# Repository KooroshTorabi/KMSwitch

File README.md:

# kmswitch

**One keyboard and mouse for two computers.** A small open-hardware box that sits between your USB
keyboard/mouse (or a wireless dongle, or a hub) and two PCs. Switch with a hotkey, or just push the
mouse off the edge of one screen and it appears on the other. No software on either PC, works in the
BIOS, and the two PCs stay galvanically isolated.

| | |
|---|---|
| Switching | hotkey (default **Win+F12**) or moving the pointer across the screen edge |
| Host software | none: the PCs see a normal USB keyboard + mouse (+ a small USB drive) |
| BIOS / boot | yes: HID Boot Protocol keyboard and mouse |
| Input | one USB-A port for any keyboard, mouse or dongle; use a hub for several devices |
| Shared drive | microSD card, shown as a USB drive on whichever PC is active |
| Power | 5 V USB-C adapter (2-3 A), so the keyboard works even if PC 1 is off |
| Isolation | CA-IS3721 digital isolator: PC 1 and PC 2 grounds never touch |
| ESD protection | USBLC6-2SC6 on the USB-A port (both variants) and on both PC USB-C ports (variant B) |
| RGB LED (optional) | 3-pin header J6 (5V, DIN, GND) for a WS2812/SK6812 LED or strip, for your own case design |

> **Status:** hardware rev 1.0 and firmware 1.0 are complete but not yet built or tested on real boards. See *Before you order* below and [firmware/README.md](firmware/README.md).

## What it does

<table>
<tr>
<td width="50%"><br>
<b>1. Copy files between the PCs</b><br>
The box's microSD card shows up as a USB drive on the active PC. Save a file there, switch, and open it on the other PC. No network or cloud needed.</td>
<td width="50%"><br>
<b>2. Switch by moving the mouse</b><br>
Push the pointer past the edge of PC 1's screen and it appears on PC 2, and the keyboard follows. You arrange the screens once on the settings page, like the monitor layout in Windows.</td>
</tr>
<tr>
<td><br>
<b>3. Switch from the keyboard</b><br>
<b>Win + F12</b> (or any key you choose) switches keyboard and mouse together. The PCs never see the hotkey. It works in the BIOS and at the login screen.</td>
<td><br>
<b>4. Game mode</b><br>
<b>Win + F11</b> switches the active PC to relative mouse movement, which games, Blender and remote-desktop tools need. Edge switching pauses so a fast flick never jumps to the other PC.</td>
</tr>
<tr>
<td><br>
<b>5. RGB LED connection</b><br>
Header J6 drives a WS2812 / SK6812 LED or short strip, lit in the colour of the active PC. Good for your own case or a desk light.</td>
<td><br>
<b>6. Separate power, isolated PCs</b><br>
The box runs from its own 5 V USB-C adapter, so the keyboard keeps working when PC 1 is off. A digital isolator keeps the grounds of the two PCs apart (no ground loops).</td>
</tr>
</table>

> Clipboard copy-paste of text would need a program on each PC. kmswitch deliberately needs no software on the PCs, so it shares files through the drive instead.

## How it works

```
 keyboard / mouse / dongle / hub
              |
          [USB-A]
              |
   MCU-A (RP2040, USB host via PIO-USB) ---- USB device ----> PC 1
              |
       UART through CA-IS3721 isolator
              |
   MCU-B (RP2040) -------------------------- USB device ----> PC 2
```

- MCU-A reads your input devices as a USB host. It sends each report either to PC 1 directly or over the isolated UART to MCU-B, which sends it to PC 2.
- To each PC, its MCU looks like a plain USB keyboard + mouse (Boot Protocol), so it works in BIOS/UEFI, login screens and any OS, with no drivers.
- **Screen-edge switching:** the mouse is reported with absolute coordinates, so the box knows when the pointer reaches the edge and hands it over to the other PC.
- **Shared drive:** the microSD card appears as a USB drive on the active PC only. On a switch the drive is ejected and shown to the other PC (media change), so the file system is never mounted twice.

## Two board variants, one choice

Both variants have the same features, the same GPIO map (so one firmware fits both) and connectors in the same places.

| | **Variant A** - RP2040-Zero carrier | **Variant B** - 2x RP2040 chip-down |
|---|---|---|
| Folder | `hardware/variant-a-rp2040-zero` | `hardware/variant-b-rp2040` |
| Board | 80 x 48 mm, 2 layers | 80 x 54 mm, 2 layers |
| MCUs | two Waveshare RP2040-Zero modules on pin headers | two RP2040 + W25Q16 flash + 12 MHz crystal |
| Assembly | hand-solderable (0805, SOIC, SOD-123, SOT-23-6) | factory assembly (JLCPCB BOM + CPL included) |
| PC connections | USB-C on the modules | USB-C on the board |
| Powered without adapter | no | yes, from PC 1 (adapter and PC 1 are OR-ed by diodes) |
| Back-feed into a switched-off PC 1 | ~4.7 V can reach PC 1 VBUS through the module | none |
| Good for | building one at home | ordering a batch, smallest result |

## Configuration (optional)

It works without any setup. To tune the mouse for different screens, change the hotkeys or add a relative mode for games, press **Win+F10**: the box opens its own settings page (`http://192.168.7.1`, served by the box over a private USB network link, any browser, nothing installed). You place PC 2 next to PC 1 by dragging, like monitors in the OS display settings, and the pointer crosses only where the screens touch. Changes are saved on the box by themselves, the page shows live which PC is connected, and the box measures each PC's monitors automatically (LEDs blink for a few seconds while it switches over and measures), including several monitors of different shape on one PC.
Where the USB network is not allowed, the same page works offline from the microSD card ([`config/KMSWITCH.HTM`](config/KMSWITCH.HTM)) together with the settings file [`config/KMSWITCH.TXT`](config/KMSWITCH.TXT).
Full reference: [docs/configuration.md](docs/configuration.md); page-to-box protocol: [docs/web-api.md](docs/web-api.md).

**Firmware updates** come from the same page (one click when a new release is out, confirmed with **Win+F8** on the box's own keyboard), from a file copied to the drive, or, as a last resort, through the RP2040's BOOTSEL mode. Updates are signed and roll back by themselves if the new version does not start: [docs/firmware-update.md](docs/firmware-update.md).

## Schematics

Each variant has one readable sheet, split into framed blocks (power input, USB ports, MCU, microSD, isolation, ...) with real wires inside each block, named power symbols (`+5V_IN`, `+3V3_A`, `GND_B`, ...) and net labels between blocks.
PDF: `hardware/<variant>/fab/kmswitch-<a|b>-schematic.pdf`. Vector versions that stay sharp at any zoom: [variant A (SVG)](docs/schematic-a.svg), [variant B (SVG)](docs/schematic-b.svg).

**Variant A** (A3 sheet), click for full size:

**Variant B** (A2 sheet), click for full size:

## Repository layout

```
hardware/
  lib/                         project symbols (RP2040-Zero, microSD), RP2040-Zero footprint,
                               3dmodels/ (detailed STEP models for parts that have none in the KiCad library)
  variant-a-rp2040-zero/       KiCad project + fab/ (gerbers zip, BOM, CPL, schematic PDF, renders)
  variant-b-rp2040/            KiCad project + fab/
config/
  KMSWITCH.TXT                 default settings file for the microSD card
  KMSWITCH.HTM                 settings page (served by the box, or offline from the card)
enclosure/
  kmswitch_case.scad           parametric 3D-printable case (variant = "A" or "B")
  stl/                         ready-to-print bottom + lid for both variants
firmware/                      (to come) firmware sources, latest.json and released update files
tools/                         Python scripts that generate the schematics, boards and outputs
docs/                          board and case renders, turntable animation, DRC reports
```

The KiCad files are saved by KiCad 7 and open in KiCad 7, 8 and 9 (newer versions convert them on save).

## Pin map (both variants)

| Function | MCU-A (host side, PC 1) | MCU-B (PC 2) |
|---|---|---|
| USB host D+ / D- (PIO-USB) | GP2 / GP3 (22 Ω series) | - |
| UART1 TX / RX (via isolator) | GP4 / GP5 | GP4 / GP5 |
| microSD SCK / MOSI / MISO / CS (SPI1) | GP14 / GP15 / GP28 / GP29 | - |
| microSD card detect | GP26 (switch to GND, use pull-up) | - |
| Status LED | GP16 WS2812 (A) / GP16-18 red, green, blue LEDs (B) | same |
| PC 1 VBUS sense (B only) | GP24 (10k/20k divider) | - |
| External RGB LED data (header J6) | GP6 (330 Ω series) | - |

PIO-USB needs D- on the pin right after D+ and a system clock that is a multiple of 12 MHz (120 MHz works).

## Building

### Variant A (hand soldering)
1. Order the PCB with `fab/kmswitch-a-gerbers.zip` (2 layers, 1.6 mm, any colour).
2. Solder the SMD parts first (`fab/kmswitch-a-bom.csv`), then the USB-A socket.
3. Solder two 1x9 male headers per module into the carrier, put the RP2040-Zero modules on top and solder them.
   Only the two long rows are used; the five pads on the module's short edge stay free.
4. The modules' USB-C ports go to the PCs. The board's own USB-C is power only (5 V adapter).

### Variant B (factory assembly)
1. Upload `fab/kmswitch-b-gerbers.zip`, `fab/kmswitch-b-bom.csv` and `fab/kmswitch-b-cpl-jlcpcb.csv` to JLCPCB (or similar).
   Every assembled part has an LCSC / JLCPCB part number in the BOM (table in `tools/export.py`). Stock changes, so check them in the JLCPCB part search before ordering. Parts marked `n/a` are not on LCSC and are hand-soldered: the RP2040-Zero modules (variant A), the through-hole USB-A (Molex 67643-0910) and the optional RGB header J6.
   In the JLCPCB placement preview, check that pin 1 of U4-U6 (SOT-23-6), U12 / U52 (SOT-23-5) and the LEDs sits on the marked pad; fix the rotation there if not.
2. Solder the USB-A socket yourself if your assembler does not place through-hole parts.
3. First flash: hold **BOOT**, tap **RST**, and drag the `.uf2` onto the drive that appears. SWD pads are next to the buttons.

### Optional RGB LED
Header **J6** (2.54 mm, labelled *RGB*): pin 1 = 5 V, pin 2 = data (GP6 of MCU-A through 330 Ω), pin 3 = GND.
Connect one WS2812B/SK6812 LED or a short chain, for example to light the side of the active PC or to glow through your own case.
Most WS2812B/SK6812 parts accept the 3.3 V data level at 5 V supply; keep the wire short (under ~20 cm). A short strip draws up to 60 mA per LED at full white, so stay within a few LEDs.
The header is not populated by the assembler; solder pins or a cable if you need it.

### Enclosure

Print `enclosure/stl/kmswitch-<a|b>-bottom.stl` and `-lid.stl` (PLA/PETG, 0.2 mm layers, no supports; the lid prints upside down).
Outside size: 85 x 53 x 21.6 mm (A) or 85 x 59 x 19.6 mm (B). Both parts together use about 35 g of filament and print in about 40 min on a fast printer (1 to 1.5 h on a Prusa MK3S / Ender 3).
Use white or translucent filament for the lid if you want the LEDs to shine through the thin windows.
Fix board and lid with four **M2.5 self-tapping screws**: 20 mm for variant A, 18 mm for variant B. They go through the lid posts and the board into the standoffs.
To change anything (wall thickness, port sizes, height), open `kmswitch_case.scad` in OpenSCAD and edit the parameters at the top.

## Before you order (please read)

- **RP2040-Zero footprint:** the header rows are drawn 15.24 mm apart with 2.54 mm pitch, pad 1 (5V) next to the USB-C.
  Measure your module or print `fab/kmswitch-a-front.png` at 1:1 and check before ordering.
- **Isolator speed:** CA-IS3721**HS** (or ADuM1201**B/C**) is fast enough for a 3 Mbaud UART. The plain ADuM1201**AR** is limited to about 1 Mbaud.
- **ERC:** KiCad 7's command line has no ERC, so the schematic was checked by comparing its netlist with the design scripts (0 differences).
  Run *Inspect → Electrical Rules Checker* once in KiCad; only "power pin not driven" style warnings should remain.
- **DRC:** both boards pass DRC with 0 errors and 0 unconnected pads, checked with KiCad 7. Two warning types are switched off on purpose: silkscreen on the board edge (connectors sit on the edge) and *footprint does not match library* (the 3D models were replaced with the ones in `hardware/lib/3dmodels`).
- The routing comes from an autorouter. It is electrically complete; tidying it by hand is welcome.

## Regenerating

```
cd tools
python3 make_lib.py           # project library
python3 sch_build.py a        # schematic only (layout in sch_a.py), checked against the design netlist
python3 build.py a            # schematic + board + autoroute (Freerouting) + DRC for variant A
python3 build.py b
python3 make_models3d.py     # build the detailed 3D models (CadQuery, STEP)
python3 make_models.py       # attach them to both boards
python3 export.py a           # gerbers, BOM, CPL, PDF, renders
openscad -D 'variant="A"' -D 'part="bottom"' -o ../enclosure/stl/kmswitch-a-bottom.stl ../enclosure/kmswitch_case.scad
```
Needs KiCad 7 with its Python module, Java, OpenSCAD and Freerouting 1.9 (put `freerouting.jar` in `tools/` or set `FREEROUTING_JAR`).
Routing runs Freerouting headless (`xvfb-run`); the result can differ slightly between runs.

## Get a ready-made one

kmswitch is a personal project. I plan to order a small batch of boards; when I have built more units than I need, I can send ready-made ones to people who cannot build one themselves, to wherever I am able to ship.
Please note: **nothing has been ordered or tested yet**, so there are no units today. The more people are interested, the cheaper each unit gets, because boards and assembly cost much less per piece in larger batches.
If you would like one, open an [issue](https://github.com/KooroshTorabi/KMSwitch/issues) titled *"I'd like one"* and say roughly where you are.

## Support the project

This is a personal project that I build in my free time. If you like it and want to help me continue, you can support me here:

- Buy Me a Coffee: https://buymeacoffee.com/kourosh
- Ko-fi: https://ko-fi.com/kourosht

## License

Hardware and enclosure: [CERN-OHL-P-2.0](https://ohwr.org/cern_ohl_p_v2.txt) (permissive). Scripts: MIT.

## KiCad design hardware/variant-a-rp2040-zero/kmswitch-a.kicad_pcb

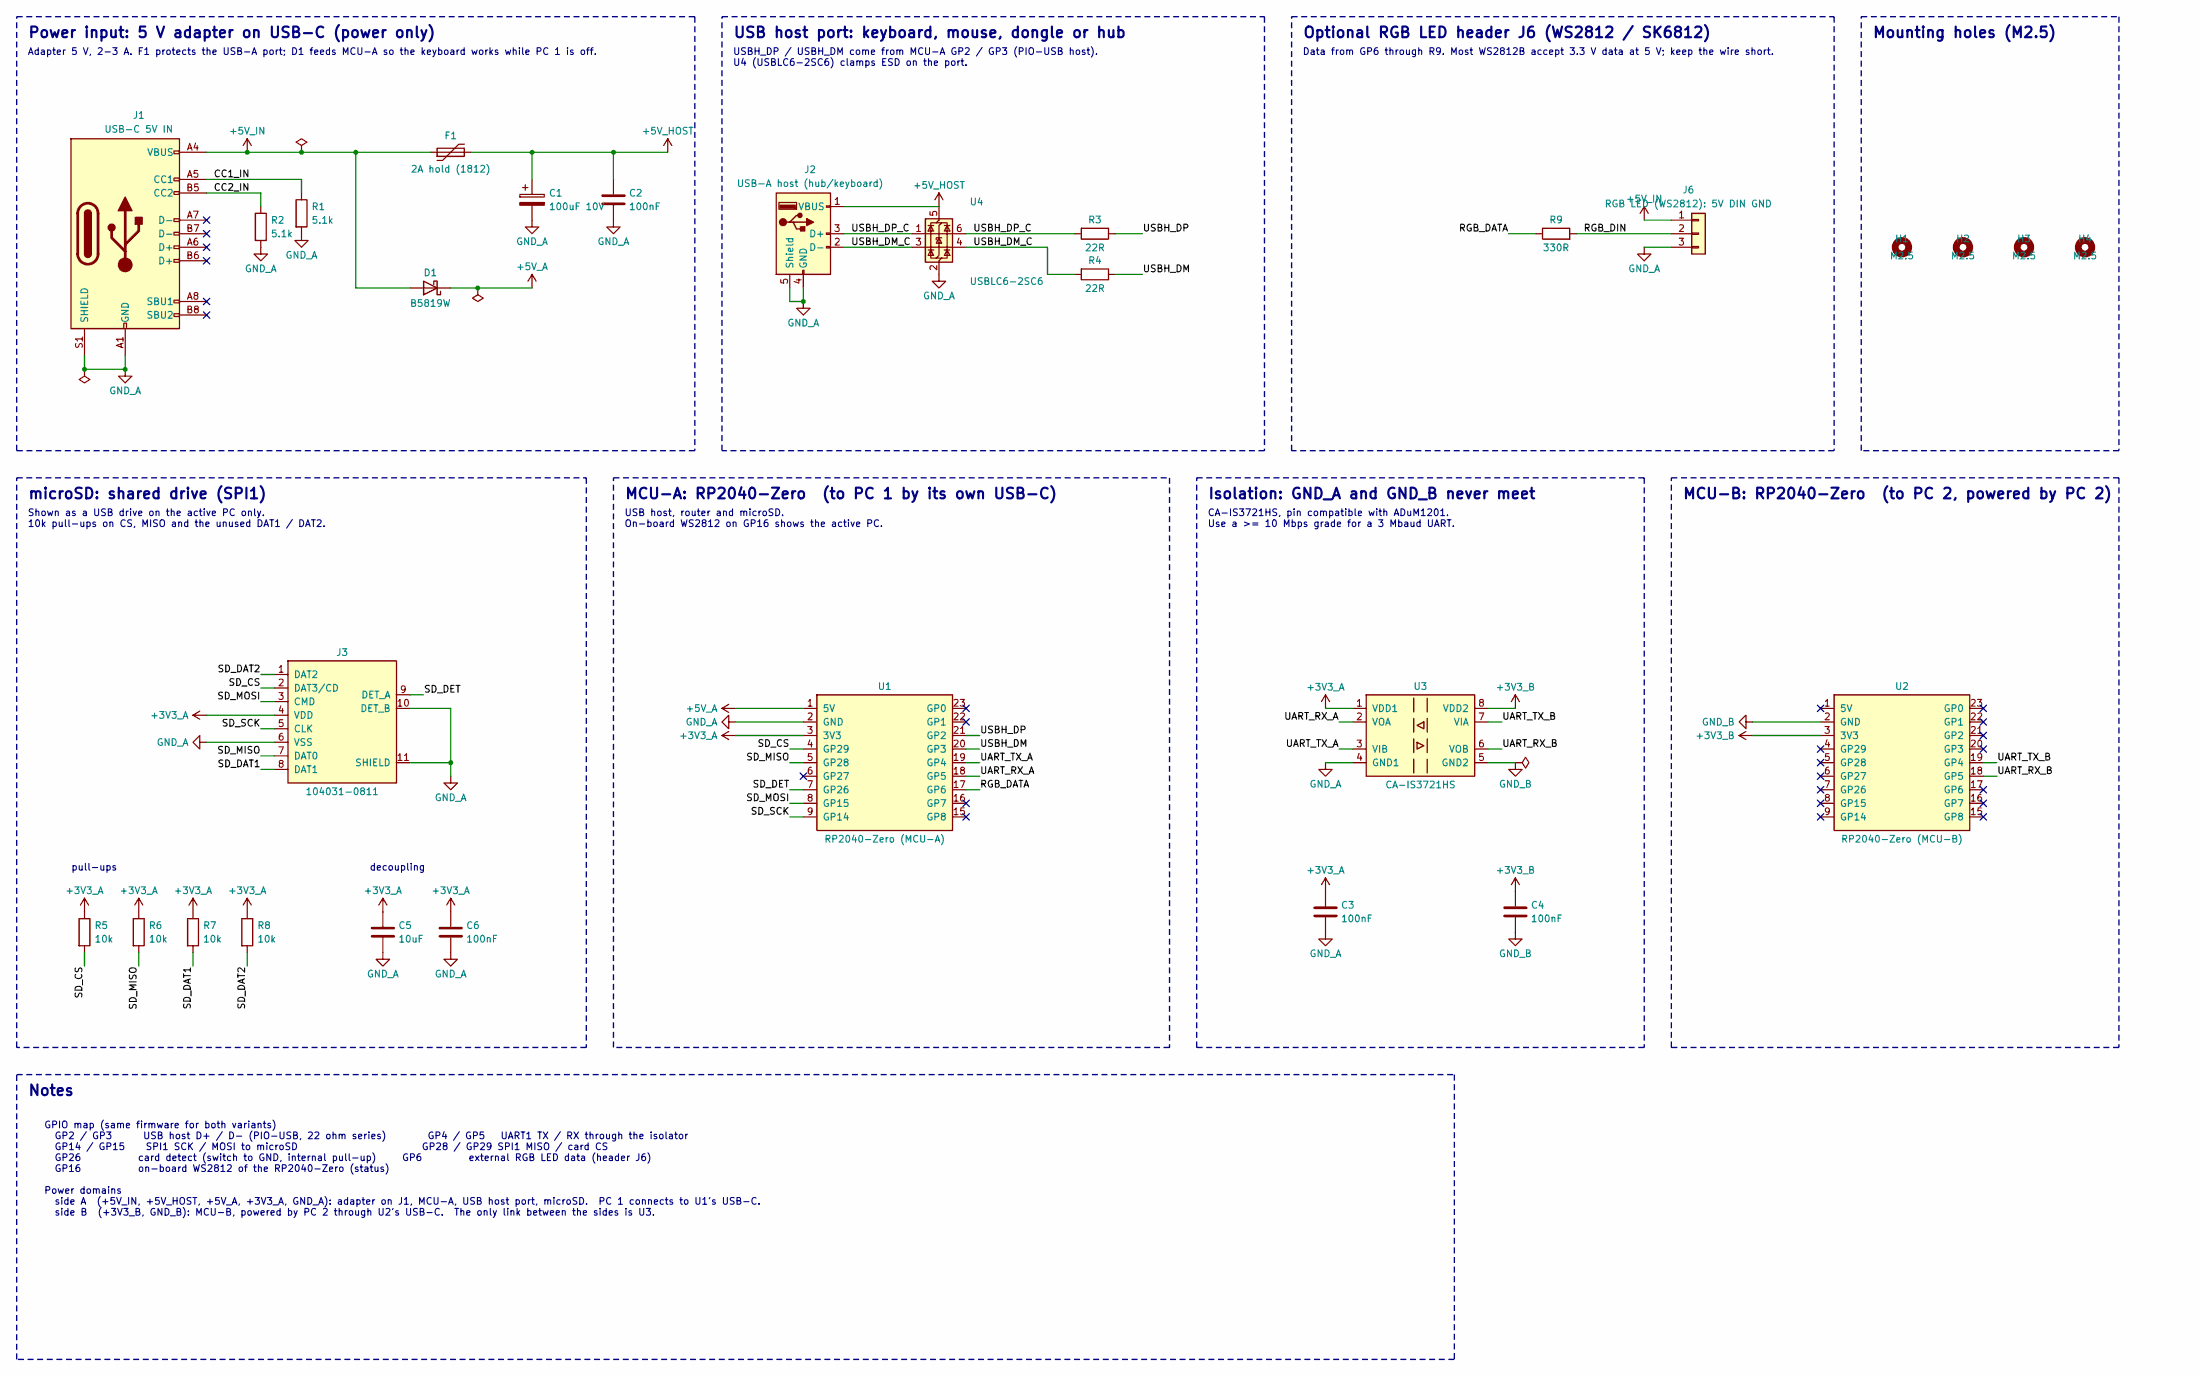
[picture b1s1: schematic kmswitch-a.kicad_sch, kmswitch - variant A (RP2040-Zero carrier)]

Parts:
C1: 100uF 10V; CP_Elec_6.3x7.7
C2, C3, C4, C6: 100nF; C_0805_2012Metric
C5: 10uF; C_0805_2012Metric
D1: B5819W; D_SOD-123
F1: 2A hold (1812); Fuse_1812_4532Metric
H1, H2, H3, H4: M2.5; MountingHole_2.7mm_M2.5
J1: USB-C 5V IN; USB_C_Receptacle_HRO_TYPE-C-31-M-12; LCSC C165948
J2: USB-A host (hub/keyboard); USB_A_Molex_67643_Horizontal
J3: 104031-0811; microSD_HC_Molex_104031-0811
J6: RGB LED (WS2812): 5V DIN GND; PinHeader_1x03_P2.54mm_Vertical
R1, R2: 5.1k; R_0805_2012Metric
R3, R4: 22R; R_0805_2012Metric
R5, R6, R7, R8: 10k; R_0805_2012Metric
R9: 330R; R_0805_2012Metric
U1: RP2040-Zero (MCU-A); RP2040-Zero_Module
U2: RP2040-Zero (MCU-B); RP2040-Zero_Module
U3: CA-IS3721HS; SOIC-8_3.9x4.9mm_P1.27mm; LCSC C428884
U4: USBLC6-2SC6; SOT-23-6; LCSC C7519

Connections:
+3V3_A: C3.1, C5.1, C6.1, J3.4 (VDD), R5.1, R6.1, R7.1, R8.1, U1.3 (3V3), U3.1 (VDD1)
+3V3_B: C4.1, U2.3 (3V3), U3.8 (VDD2)
+5V_A: D1.1 (K), U1.1 (5V)
+5V_HOST: C1.1, C2.1, F1.2, J2.1 (VBUS), U4.5 (VBUS)
+5V_IN: D1.2 (A), F1.1, J1.A4 (VBUS), J1.A9 (VBUS), J1.B4 (VBUS), J1.B9 (VBUS), J6.1
CC1_IN: J1.A5 (CC1), R1.1
CC2_IN: J1.B5 (CC2), R2.1
GND_A: C1.2, C2.2, C3.2, C5.2, C6.2, J1.A1 (GND), J1.A12 (GND), J1.B1 (GND), J1.B12 (GND), J1.S1 (SHIELD), J2.4 (GND), J2.5 (Shield), J3.6 (VSS), J3.10 (DET_B), J3.11 (SHIELD), J6.3, R1.2, R2.2, U1.2 (GND), U3.4 (GND1), U4.2 (GND)
GND_B: C4.2, U2.2 (GND), U3.5 (GND2)
RGB_DATA: R9.1, U1.17 (GP6)
RGB_DIN: J6.2, R9.2
SD_CS: J3.2 (DAT3/CD), R5.2, U1.4 (GP29)
SD_DAT1: J3.8 (DAT1), R7.2
SD_DAT2: J3.1 (DAT2), R8.2
SD_DET: J3.9 (DET_A), U1.7 (GP26)
SD_MISO: J3.7 (DAT0), R6.2, U1.5 (GP28)
SD_MOSI: J3.3 (CMD), U1.8 (GP15)
SD_SCK: J3.5 (CLK), U1.9 (GP14)
UART_RX_A: U1.18 (GP5), U3.2 (VOA)
UART_RX_B: U2.18 (GP5), U3.6 (VOB)
UART_TX_A: U1.19 (GP4), U3.3 (VIB)
UART_TX_B: U2.19 (GP4), U3.7 (VIA)
USBH_DM: R4.1, U1.20 (GP3)
USBH_DM_C: J2.2 (D-), R4.2, U4.3 (I/O2), U4.4 (I/O2)
USBH_DP: R3.1, U1.21 (GP2)
USBH_DP_C: J2.3 (D+), R3.2, U4.1 (I/O1), U4.6 (I/O1)

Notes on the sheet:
Power input: 5 V adapter on USB-C (power only)
Adapter 5 V, 2-3 A. F1 protects the USB-A port; D1 feeds MCU-A so the keyboard works while PC 1 is off.
USB host port: keyboard, mouse, dongle or hub
USBH_DP / USBH_DM come from MCU-A GP2 / GP3 (PIO-USB host). U4 (USBLC6-2SC6) clamps ESD on the port.
Optional RGB LED header J6 (WS2812 / SK6812)
Data from GP6 through R9. Most WS2812B accept 3.3 V data at 5 V; keep the wire short.
Mounting holes (M2.5)
microSD: shared drive (SPI1)
Shown as a USB drive on the active PC only. 10k pull-ups on CS, MISO and the unused DAT1 / DAT2.
pull-ups
decoupling
MCU-A: RP2040-Zero (to PC 1 by its own USB-C)
USB host, router and microSD. On-board WS2812 on GP16 shows the active PC.
Isolation: GND_A and GND_B never meet
CA-IS3721HS, pin compatible with ADuM1201. Use a >= 10 Mbps grade for a 3 Mbaud UART.
MCU-B: RP2040-Zero (to PC 2, powered by PC 2)
Notes
GPIO map (same firmware for both variants) GP2 / GP3 USB host D+ / D- (PIO-USB, 22 ohm series) GP4 / GP5 UART1 TX / RX through the isolator GP14 / GP15 SPI1 SCK / MOSI to microSD GP28 / GP29 SPI1 MISO / card CS GP26 card detect (switch to GND, internal pull-up) GP6 external RGB LED data (header J6)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

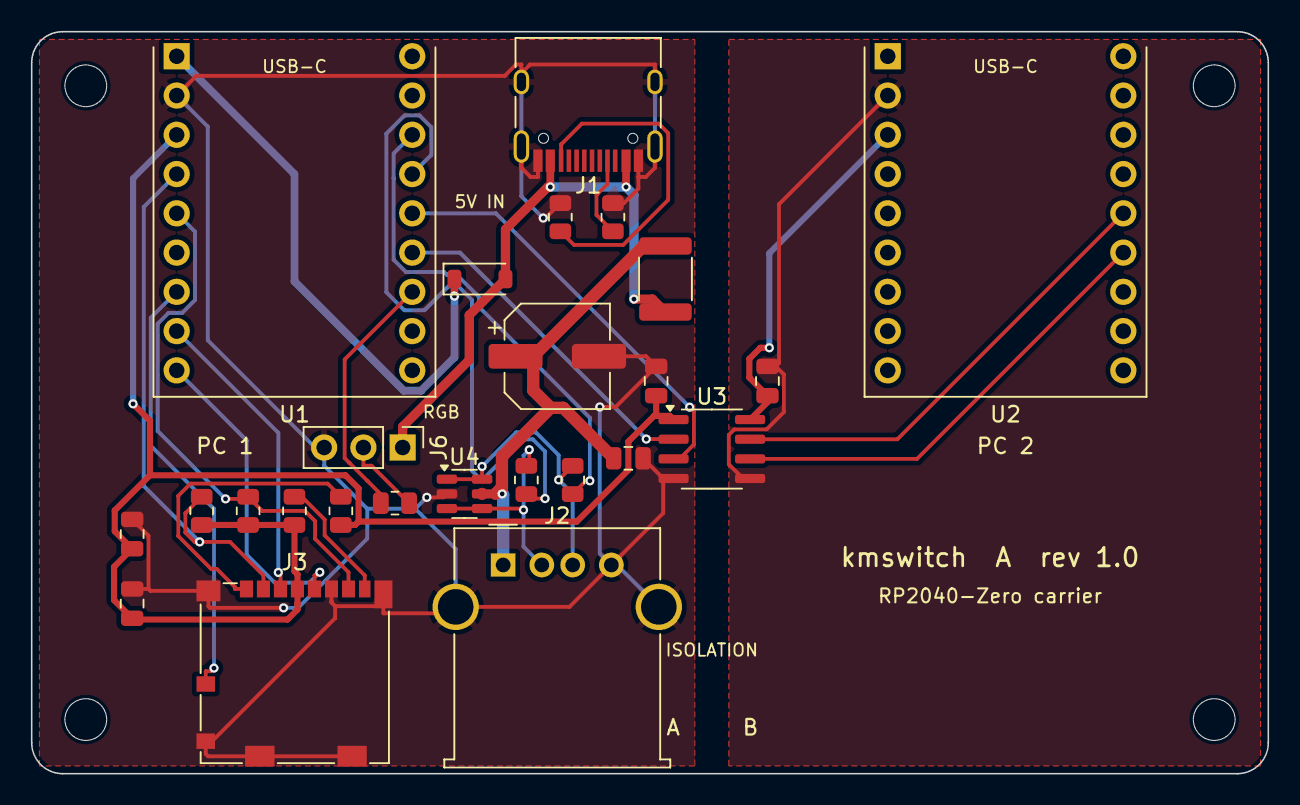
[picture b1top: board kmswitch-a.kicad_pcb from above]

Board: 2 copper layers, 80.0 x 48.0 mm, 29 parts (0 on the bottom side), 26 nets.

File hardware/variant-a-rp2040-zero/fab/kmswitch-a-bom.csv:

Comment,Designator,Footprint,Quantity,LCSC Part #,Notes
100uF 10V,C1,CP_Elec_6.3x7.7,1,C294520,"VT1V101M-CRE77, 100uF 35V 6.3x7.7 (higher voltage is fine)"
100nF,"C2,C3,C4,C6",C_0805_2012Metric,4,C49678,
10uF,C5,C_0805_2012Metric,1,C15850,
B5819W,D1,D_SOD-123,1,C8598,
2A hold (1812),F1,Fuse_1812_4532Metric,1,C545213,"SMD1812P200TF/16, 2A hold 16V"
USB-C 5V IN,J1,USB_C_Receptacle_HRO_TYPE-C-31-M-12,1,C165948,
USB-A host (hub/keyboard),J2,USB_A_Molex_67643_Horizontal,1,n/a,"Molex 67643-0910 through-hole (Mouser/DigiKey/TME), hand-solder"
104031-0811,J3,microSD_HC_Molex_104031-0811,1,C585350,
RGB LED (WS2812): 5V DIN GND,J6,PinHeader_1x03_P2.54mm_Vertical,1,n/a,"optional 3-pin header, not assembled (DNP)"
5.1k,"R1,R2",R_0805_2012Metric,2,C27834,
22R,"R3,R4",R_0805_2012Metric,2,C17561,
10k,"R5,R6,R7,R8",R_0805_2012Metric,4,C17414,
330R,R9,R_0805_2012Metric,1,C17630,
RP2040-Zero (MCU-A),U1,RP2040-Zero_Module,1,n/a,"Waveshare RP2040-Zero module (not on LCSC) + 2x 1x9 pin headers, hand-solder"
RP2040-Zero (MCU-B),U2,RP2040-Zero_Module,1,n/a,"Waveshare RP2040-Zero module (not on LCSC) + 2x 1x9 pin headers, hand-solder"
CA-IS3721HS,U3,SOIC-8_3.9x4.9mm_P1.27mm,1,C428884,
USBLC6-2SC6,U4,SOT-23-6,1,C7519,

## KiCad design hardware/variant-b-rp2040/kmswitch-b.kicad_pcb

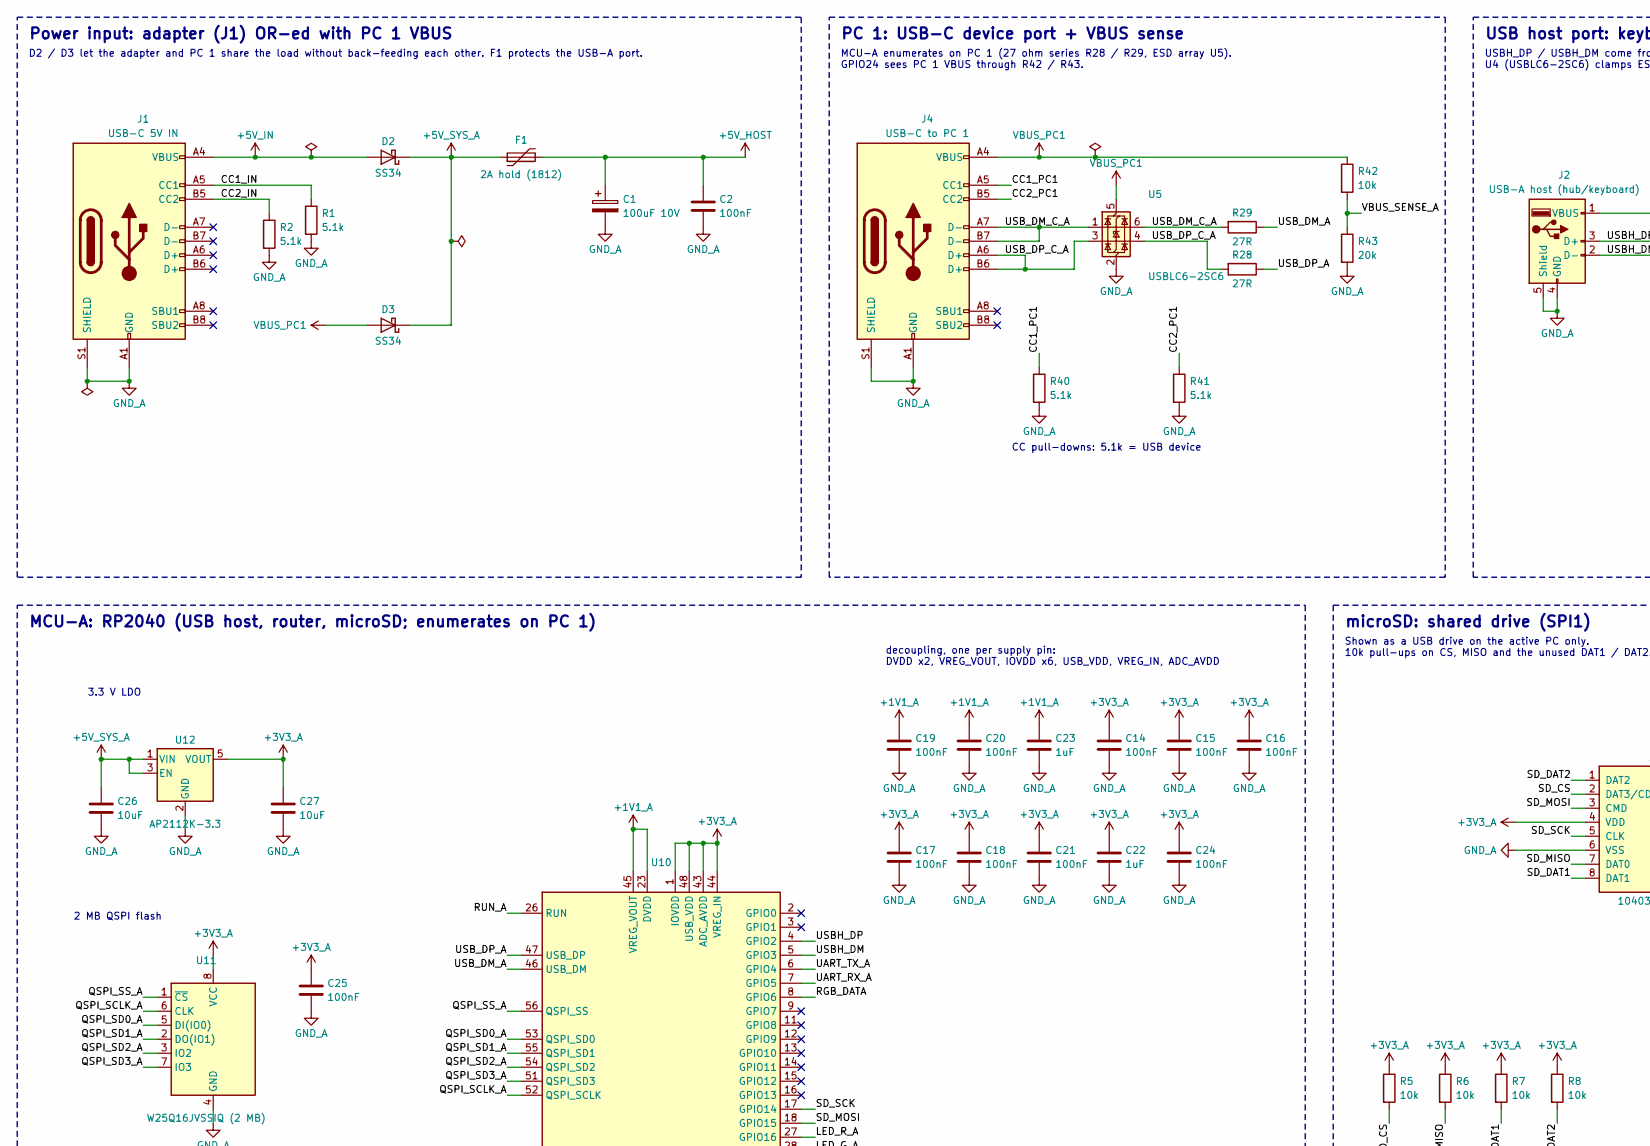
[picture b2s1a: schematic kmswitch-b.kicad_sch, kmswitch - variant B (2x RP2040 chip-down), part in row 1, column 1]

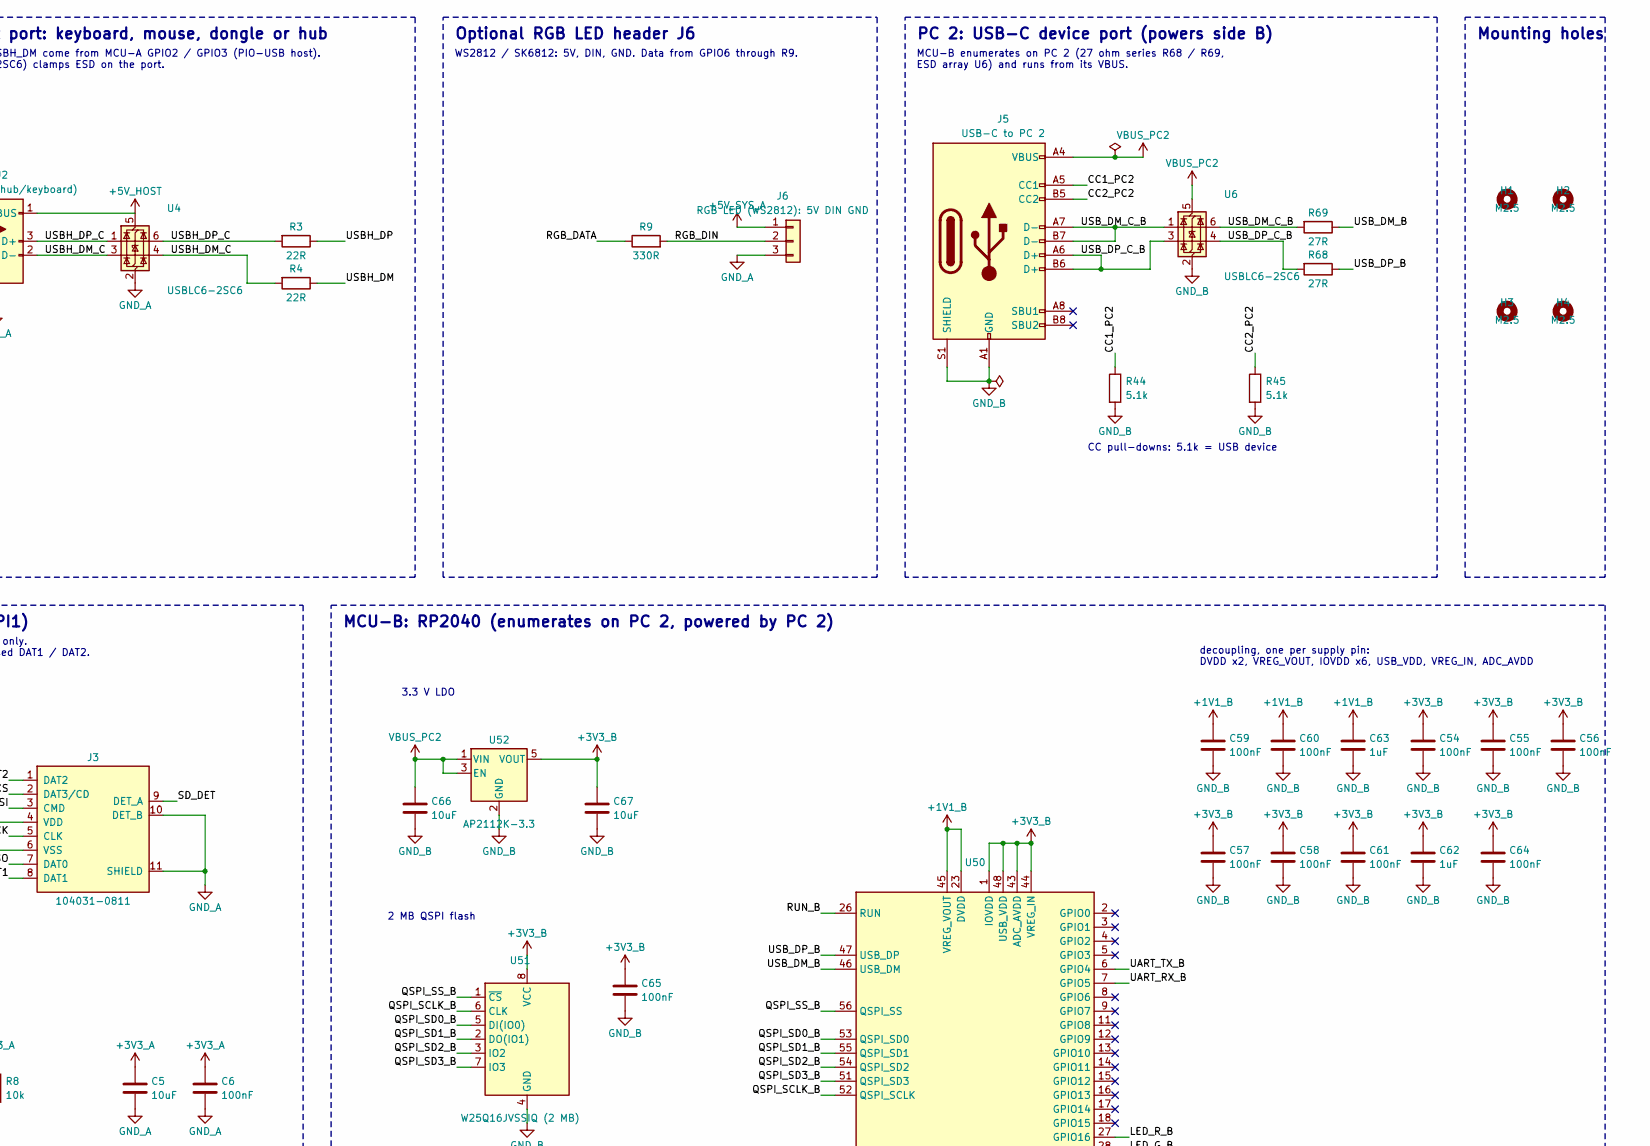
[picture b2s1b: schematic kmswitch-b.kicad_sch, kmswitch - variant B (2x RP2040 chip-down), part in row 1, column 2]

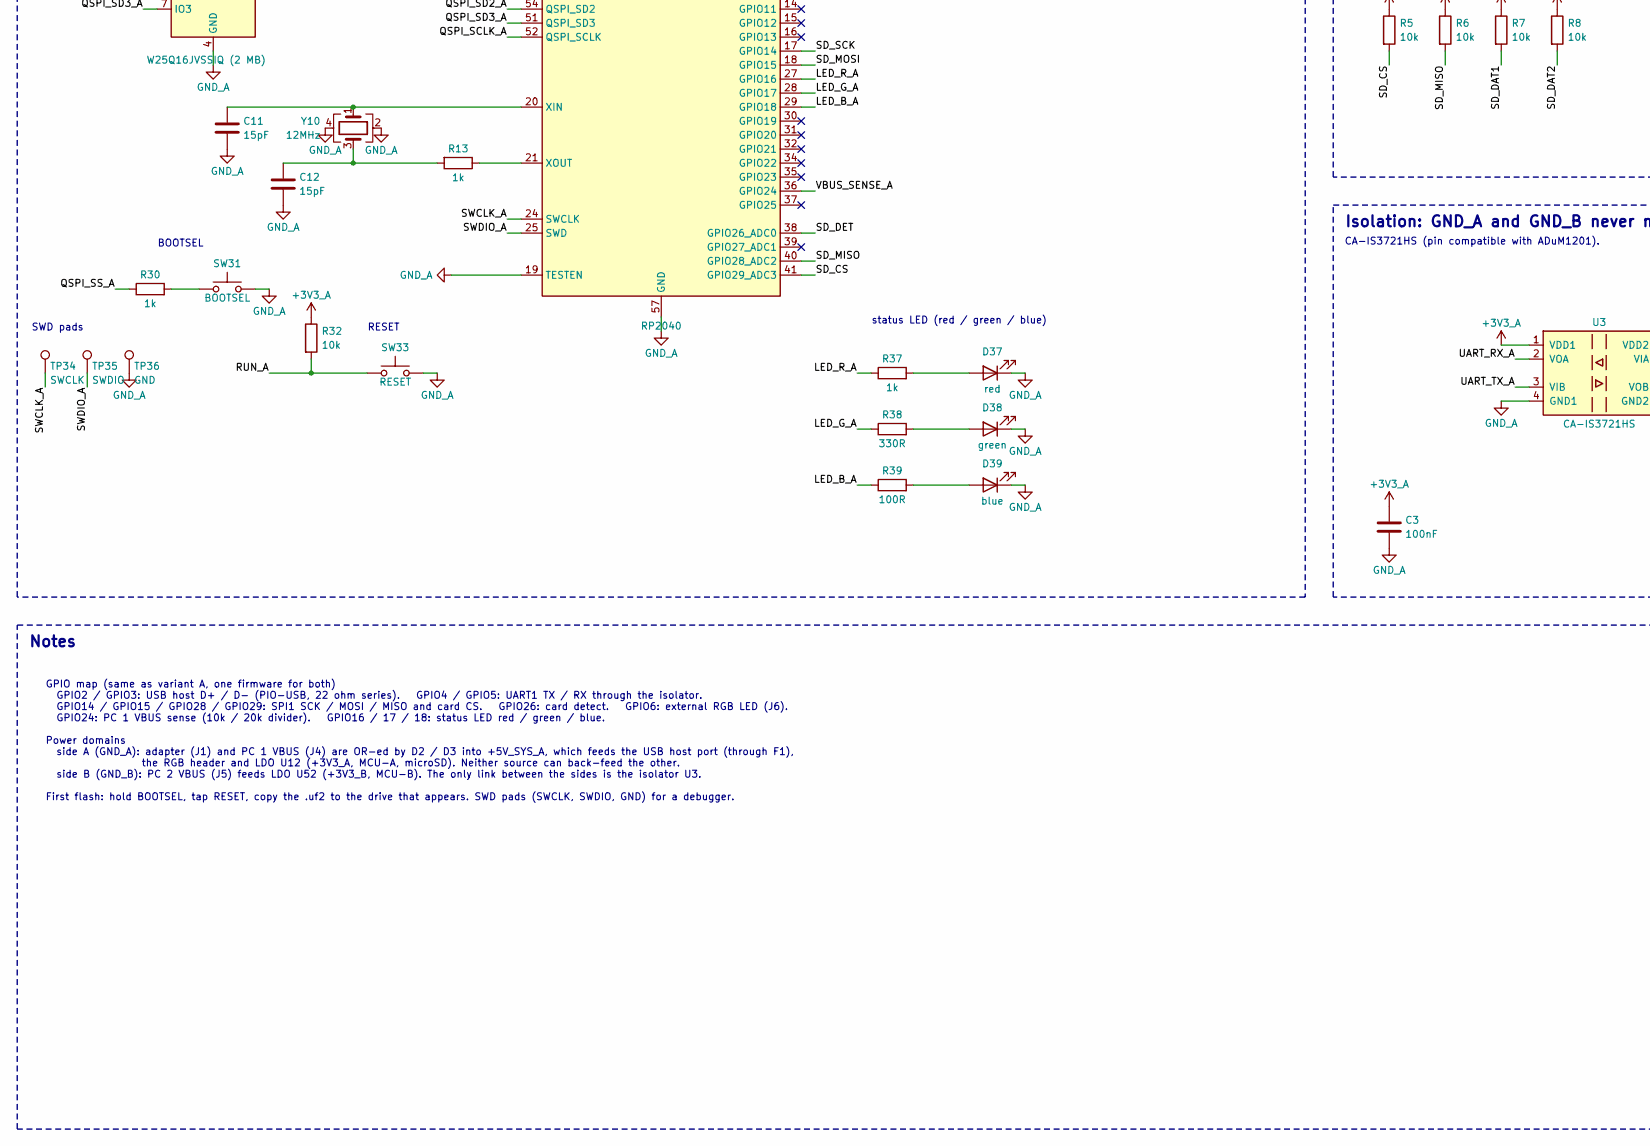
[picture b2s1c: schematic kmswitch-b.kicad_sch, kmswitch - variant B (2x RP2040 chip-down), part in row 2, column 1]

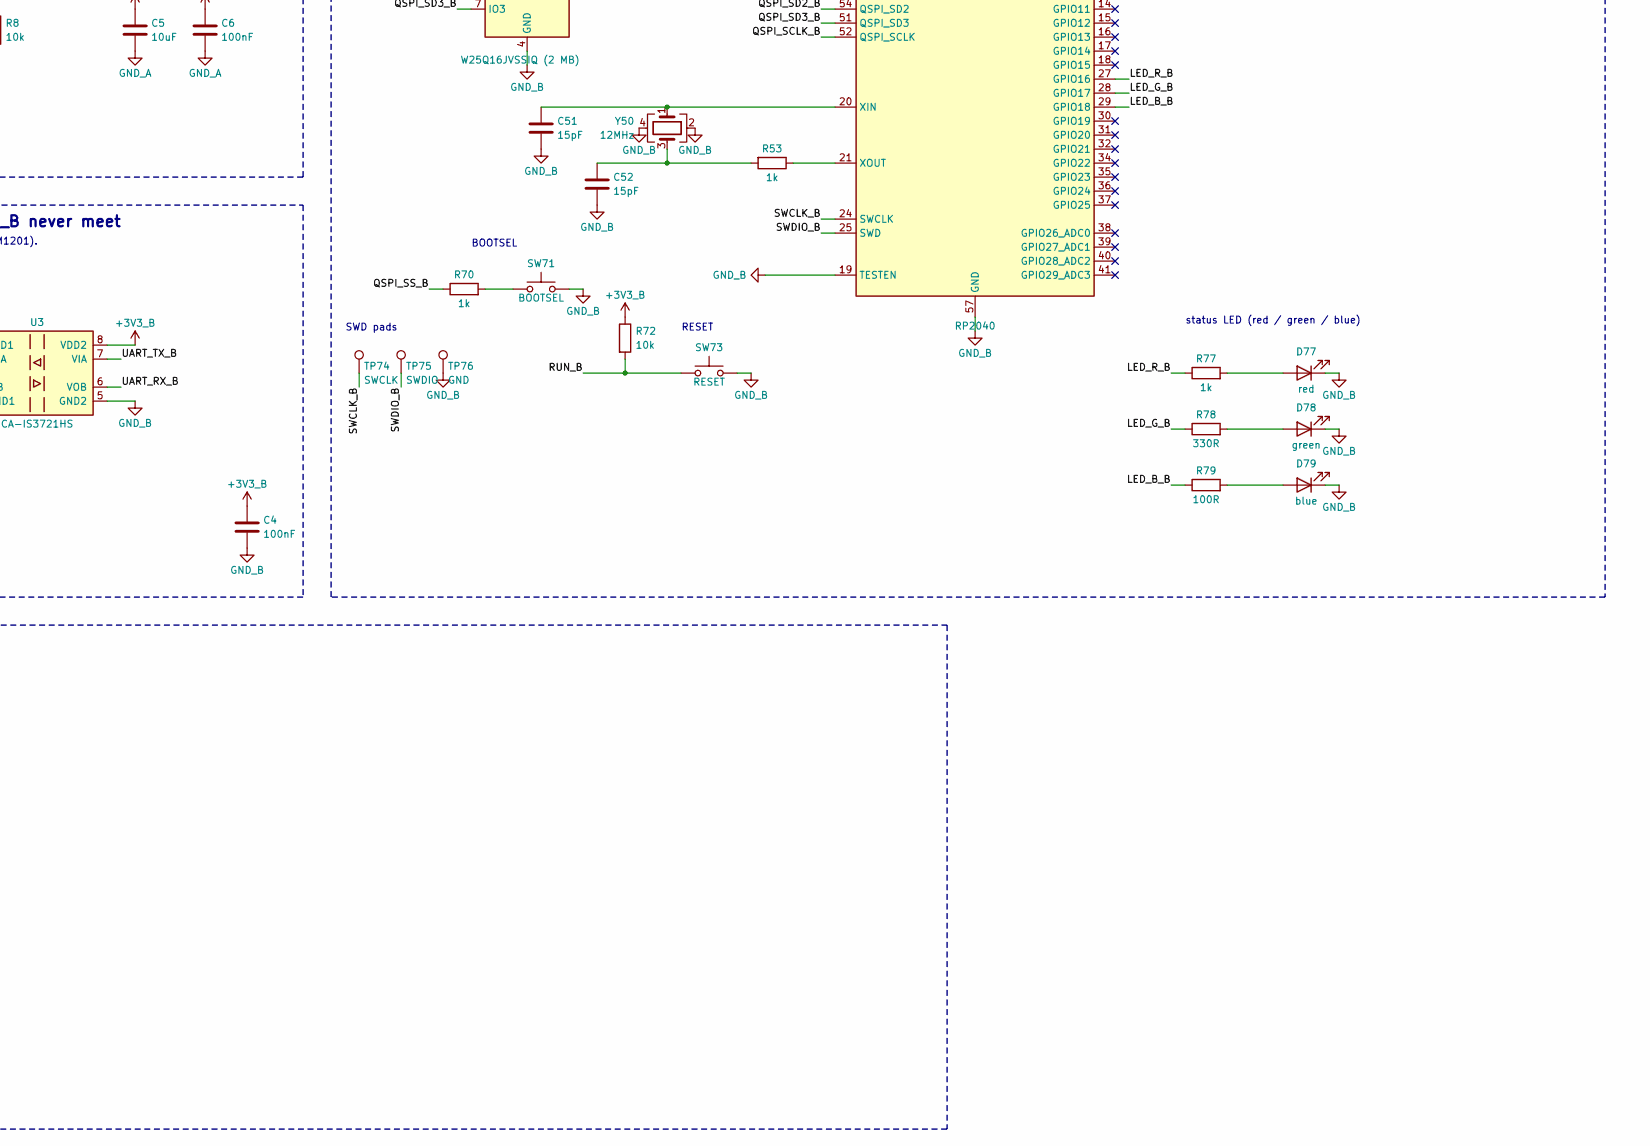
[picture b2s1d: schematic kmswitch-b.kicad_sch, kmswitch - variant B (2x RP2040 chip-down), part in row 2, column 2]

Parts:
C1: 100uF 10V; CP_Elec_6.3x7.7
C2: 100nF; C_0805_2012Metric
C3, C4, C6, C14, C15, C16, C17, C18, C19, C20, C21, C24, C25, C54, C55, C56, C57, C58, C59, C60, C61, C64, C65: 100nF; C_0603_1608Metric
C5, C26, C27, C66, C67: 10uF; C_0805_2012Metric
C11, C12, C51, C52: 15pF; C_0603_1608Metric
C22, C23, C62, C63: 1uF; C_0603_1608Metric
D2, D3: SS34; D_SMA; LCSC C8678
D37, D77: red; LED_0603_1608Metric
D38, D78: green; LED_0603_1608Metric
D39, D79: blue; LED_0603_1608Metric
F1: 2A hold (1812); Fuse_1812_4532Metric
H1, H2, H3, H4: M2.5; MountingHole_2.7mm_M2.5
J1: USB-C 5V IN; USB_C_Receptacle_HRO_TYPE-C-31-M-12; LCSC C165948
J2: USB-A host (hub/keyboard); USB_A_Molex_67643_Horizontal
J3: 104031-0811; microSD_HC_Molex_104031-0811
J4: USB-C to PC 1; USB_C_Receptacle_HRO_TYPE-C-31-M-12; LCSC C165948
J5: USB-C to PC 2; USB_C_Receptacle_HRO_TYPE-C-31-M-12; LCSC C165948
J6: RGB LED (WS2812): 5V DIN GND; PinHeader_1x03_P2.54mm_Vertical
R1, R2: 5.1k; R_0805_2012Metric
R3, R4: 22R; R_0603_1608Metric
R5, R6, R7, R8, R32, R42, R72: 10k; R_0603_1608Metric
R9, R38, R78: 330R; R_0603_1608Metric
R13, R30, R37, R53, R70, R77: 1k; R_0603_1608Metric
R28, R29, R68, R69: 27R; R_0603_1608Metric
R39, R79: 100R; R_0603_1608Metric
R40, R41, R44, R45: 5.1k; R_0603_1608Metric
R43: 20k; R_0603_1608Metric
SW31, SW71: BOOTSEL; SW_SPST_PTS810
SW33, SW73: RESET; SW_SPST_PTS810
TP34, TP74: SWCLK; TestPoint_Pad_D1.0mm
TP35, TP75: SWDIO; TestPoint_Pad_D1.0mm
TP36, TP76: GND; TestPoint_Pad_D1.0mm
U3: CA-IS3721HS; SOIC-8_3.9x4.9mm_P1.27mm; LCSC C428884
U4, U5, U6: USBLC6-2SC6; SOT-23-6; LCSC C7519
U10, U50: RP2040; QFN-56-1EP_7x7mm_P0.4mm_EP3.2x3.2mm; LCSC C2040
U11, U51: W25Q16JVSSIQ (2 MB); SOIC-8_5.23x5.23mm_P1.27mm; LCSC C131024
U12, U52: AP2112K-3.3; SOT-23-5; LCSC C51118
Y10, Y50: 12MHz; Crystal_SMD_3225-4Pin_3.2x2.5mm; LCSC C9002

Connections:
+1V1_A: C19.1, C20.1, C23.1, U10.23 (DVDD), U10.45 (VREG_VOUT), U10.50 (DVDD)
+1V1_B: C59.1, C60.1, C63.1, U50.23 (DVDD), U50.45 (VREG_VOUT), U50.50 (DVDD)
+3V3_A: C3.1, C5.1, C6.1, C14.1, C15.1, C16.1, C17.1, C18.1, C21.1, C22.1, C24.1, C25.1, C27.1, J3.4 (VDD), R5.1, R6.1, R7.1, R8.1, R32.1, U3.1 (VDD1), U10.1 (IOVDD), U10.10 (IOVDD), U10.22 (IOVDD), U10.33 (IOVDD), U10.42 (IOVDD), U10.43 (ADC_AVDD), U10.44 (VREG_IN), U10.48 (USB_VDD), U10.49 (IOVDD), U11.8 (VCC), U12.5 (VOUT)
+3V3_B: C4.1, C54.1, C55.1, C56.1, C57.1, C58.1, C61.1, C62.1, C64.1, C65.1, C67.1, R72.1, U3.8 (VDD2), U50.1 (IOVDD), U50.10 (IOVDD), U50.22 (IOVDD), U50.33 (IOVDD), U50.42 (IOVDD), U50.43 (ADC_AVDD), U50.44 (VREG_IN), U50.48 (USB_VDD), U50.49 (IOVDD), U51.8 (VCC), U52.5 (VOUT)
+5V_HOST: C1.1, C2.1, F1.2, J2.1 (VBUS), U4.5 (VBUS)
+5V_IN: D2.2 (A), J1.A4 (VBUS), J1.A9 (VBUS), J1.B4 (VBUS), J1.B9 (VBUS)
+5V_SYS_A: C26.1, D2.1 (K), D3.1 (K), F1.1, J6.1, U12.1 (VIN), U12.3 (EN)
BOOT_A: R30.2, SW31.1
BOOT_B: R70.2, SW71.1
CC1_IN: J1.A5 (CC1), R1.1
CC1_PC1: J4.A5 (CC1), R40.1
CC1_PC2: J5.A5 (CC1), R44.1
CC2_IN: J1.B5 (CC2), R2.1
CC2_PC1: J4.B5 (CC2), R41.1
CC2_PC2: J5.B5 (CC2), R45.1
GND_A: C1.2, C2.2, C3.2, C5.2, C6.2, C11.2, C12.2, C14.2, C15.2, C16.2, C17.2, C18.2, C19.2, C20.2, C21.2, C22.2, C23.2, C24.2, C25.2, C26.2, C27.2, D37.1 (K), D38.1 (K), D39.1 (K), J1.A1 (GND), J1.A12 (GND), J1.B1 (GND), J1.B12 (GND), J1.S1 (SHIELD), J2.4 (GND), J2.5 (Shield), J3.6 (VSS), J3.10 (DET_B), J3.11 (SHIELD), J4.A1 (GND), J4.A12 (GND), J4.B1 (GND), J4.B12 (GND), J4.S1 (SHIELD), J6.3, R1.2, R2.2, R40.2, R41.2, R43.2, SW31.2, SW33.2, TP36.1, U3.4 (GND1), U4.2 (GND), U5.2 (GND), U10.19 (TESTEN), U10.57 (GND), U11.4 (GND), U12.2 (GND), Y10.2, Y10.4
GND_B: C4.2, C51.2, C52.2, C54.2, C55.2, C56.2, C57.2, C58.2, C59.2, C60.2, C61.2, C62.2, C63.2, C64.2, C65.2, C66.2, C67.2, D77.1 (K), D78.1 (K), D79.1 (K), J5.A1 (GND), J5.A12 (GND), J5.B1 (GND), J5.B12 (GND), J5.S1 (SHIELD), R44.2, R45.2, SW71.2, SW73.2, TP76.1, U3.5 (GND2), U6.2 (GND), U50.19 (TESTEN), U50.57 (GND), U51.4 (GND), U52.2 (GND), Y50.2, Y50.4
LED_BA_A: D39.2 (A), R39.2
LED_BA_B: D79.2 (A), R79.2
LED_B_A: R39.1, U10.29 (GPIO18)
LED_B_B: R79.1, U50.29 (GPIO18)
LED_GA_A: D38.2 (A), R38.2
LED_GA_B: D78.2 (A), R78.2
LED_G_A: R38.1, U10.28 (GPIO17)
LED_G_B: R78.1, U50.28 (GPIO17)
LED_RA_A: D37.2 (A), R37.2
LED_RA_B: D77.2 (A), R77.2
LED_R_A: R37.1, U10.27 (GPIO16)
LED_R_B: R77.1, U50.27 (GPIO16)
QSPI_SCLK_A: U10.52 (QSPI_SCLK), U11.6 (CLK)
QSPI_SCLK_B: U50.52 (QSPI_SCLK), U51.6 (CLK)
QSPI_SD0_A: U10.53 (QSPI_SD0), U11.5 (DI(IO0))
QSPI_SD0_B: U50.53 (QSPI_SD0), U51.5 (DI(IO0))
QSPI_SD1_A: U10.55 (QSPI_SD1), U11.2 (DO(IO1))
QSPI_SD1_B: U50.55 (QSPI_SD1), U51.2 (DO(IO1))
QSPI_SD2_A: U10.54 (QSPI_SD2), U11.3 (IO2)
QSPI_SD2_B: U50.54 (QSPI_SD2), U51.3 (IO2)
QSPI_SD3_A: U10.51 (QSPI_SD3), U11.7 (IO3)
QSPI_SD3_B: U50.51 (QSPI_SD3), U51.7 (IO3)
QSPI_SS_A: R30.1, U10.56 (QSPI_SS), U11.1 (~CS)
QSPI_SS_B: R70.1, U50.56 (QSPI_SS), U51.1 (~CS)
RGB_DATA: R9.1, U10.8 (GPIO6)
RGB_DIN: J6.2, R9.2
RUN_A: R32.2, SW33.1, U10.26 (RUN)
RUN_B: R72.2, SW73.1, U50.26 (RUN)
SD_CS: J3.2 (DAT3/CD), R5.2, U10.41 (GPIO29_ADC3)
SD_DAT1: J3.8 (DAT1), R7.2
SD_DAT2: J3.1 (DAT2), R8.2
SD_DET: J3.9 (DET_A), U10.38 (GPIO26_ADC0)
SD_MISO: J3.7 (DAT0), R6.2, U10.40 (GPIO28_ADC2)
SD_MOSI: J3.3 (CMD), U10.18 (GPIO15)
SD_SCK: J3.5 (CLK), U10.17 (GPIO14)
SWCLK_A: TP34.1, U10.24 (SWCLK)
SWCLK_B: TP74.1, U50.24 (SWCLK)
SWDIO_A: TP35.1, U10.25 (SWD)
SWDIO_B: TP75.1, U50.25 (SWD)
UART_RX_A: U3.2 (VOA), U10.7 (GPIO5)
UART_RX_B: U3.6 (VOB), U50.7 (GPIO5)
UART_TX_A: U3.3 (VIB), U10.6 (GPIO4)
UART_TX_B: U3.7 (VIA), U50.6 (GPIO4)
USBH_DM: R4.1, U10.5 (GPIO3)
USBH_DM_C: J2.2 (D-), R4.2, U4.3 (I/O2), U4.4 (I/O2)
USBH_DP: R3.1, U10.4 (GPIO2)
USBH_DP_C: J2.3 (D+), R3.2, U4.1 (I/O1), U4.6 (I/O1)
USB_DM_A: R29.1, U10.46 (USB_DM)
USB_DM_B: R69.1, U50.46 (USB_DM)
USB_DM_C_A: J4.A7 (D-), J4.B7 (D-), R29.2, U5.1 (I/O1), U5.6 (I/O1)
USB_DM_C_B: J5.A7 (D-), J5.B7 (D-), R69.2, U6.1 (I/O1), U6.6 (I/O1)
USB_DP_A: R28.1, U10.47 (USB_DP)
USB_DP_B: R68.1, U50.47 (USB_DP)
USB_DP_C_A: J4.A6 (D+), J4.B6 (D+), R28.2, U5.3 (I/O2), U5.4 (I/O2)
USB_DP_C_B: J5.A6 (D+), J5.B6 (D+), R68.2, U6.3 (I/O2), U6.4 (I/O2)
VBUS_PC1: D3.2 (A), J4.A4 (VBUS), J4.A9 (VBUS), J4.B4 (VBUS), J4.B9 (VBUS), R42.1, U5.5 (VBUS)
VBUS_PC2: C66.1, J5.A4 (VBUS), J5.A9 (VBUS), J5.B4 (VBUS), J5.B9 (VBUS), U6.5 (VBUS), U52.1 (VIN), U52.3 (EN)
VBUS_SENSE_A: R42.2, R43.1, U10.36 (GPIO24)
XIN_A: C11.1, U10.20 (XIN), Y10.1
XIN_B: C51.1, U50.20 (XIN), Y50.1
XOUT_A: R13.1, U10.21 (XOUT)
XOUT_B: R53.1, U50.21 (XOUT)
XOUT_R_A: C12.1, R13.2, Y10.3
XOUT_R_B: C52.1, R53.2, Y50.3

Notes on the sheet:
Power input: adapter (J1) OR-ed with PC 1 VBUS
D2 / D3 let the adapter and PC 1 share the load without back-feeding each other. F1 protects the USB-A port.
PC 1: USB-C device port + VBUS sense
MCU-A enumerates on PC 1 (27 ohm series R28 / R29, ESD array U5). GPIO24 sees PC 1 VBUS through R42 / R43.
CC pull-downs: 5.1k = USB device
USB host port: keyboard, mouse, dongle or hub
USBH_DP / USBH_DM come from MCU-A GPIO2 / GPIO3 (PIO-USB host). U4 (USBLC6-2SC6) clamps ESD on the port.
Optional RGB LED header J6
WS2812 / SK6812: 5V, DIN, GND. Data from GPIO6 through R9.
PC 2: USB-C device port (powers side B)
MCU-B enumerates on PC 2 (27 ohm series R68 / R69, ESD array U6) and runs from its VBUS.
Mounting holes
MCU-A: RP2040 (USB host, router, microSD; enumerates on PC 1)
2 MB QSPI flash
3.3 V LDO
decoupling, one per supply pin: DVDD x2, VREG_VOUT, IOVDD x6, USB_VDD, VREG_IN, ADC_AVDD
BOOTSEL
RESET
SWD pads
status LED (red / green / blue)
microSD: shared drive (SPI1)
Shown as a USB drive on the active PC only. 10k pull-ups on CS, MISO and the unused DAT1 / DAT2.
Isolation: GND_A and GND_B never meet
CA-IS3721HS (pin compatible with ADuM1201).
MCU-B: RP2040 (enumerates on PC 2, powered by PC 2)
Notes
GPIO map (same as variant A, one firmware for both) GPIO2 / GPIO3: USB host D+ / D- (PIO-USB, 22 ohm series). GPIO4 / GPIO5: UART1 TX / RX through the isolator. GPIO14 / GPIO15 / GPIO28 / GPIO29: SPI1 SCK / MOSI / MISO and card CS. GPIO26: card detect. GPIO6: external RGB LED (J6). GPIO24: PC 1 VBU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

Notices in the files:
README.md:
Hardware: CERN-OHL-P-2.0
